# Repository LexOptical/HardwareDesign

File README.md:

# HardwareDesign
The LEX hardware design, electrical and mechanical

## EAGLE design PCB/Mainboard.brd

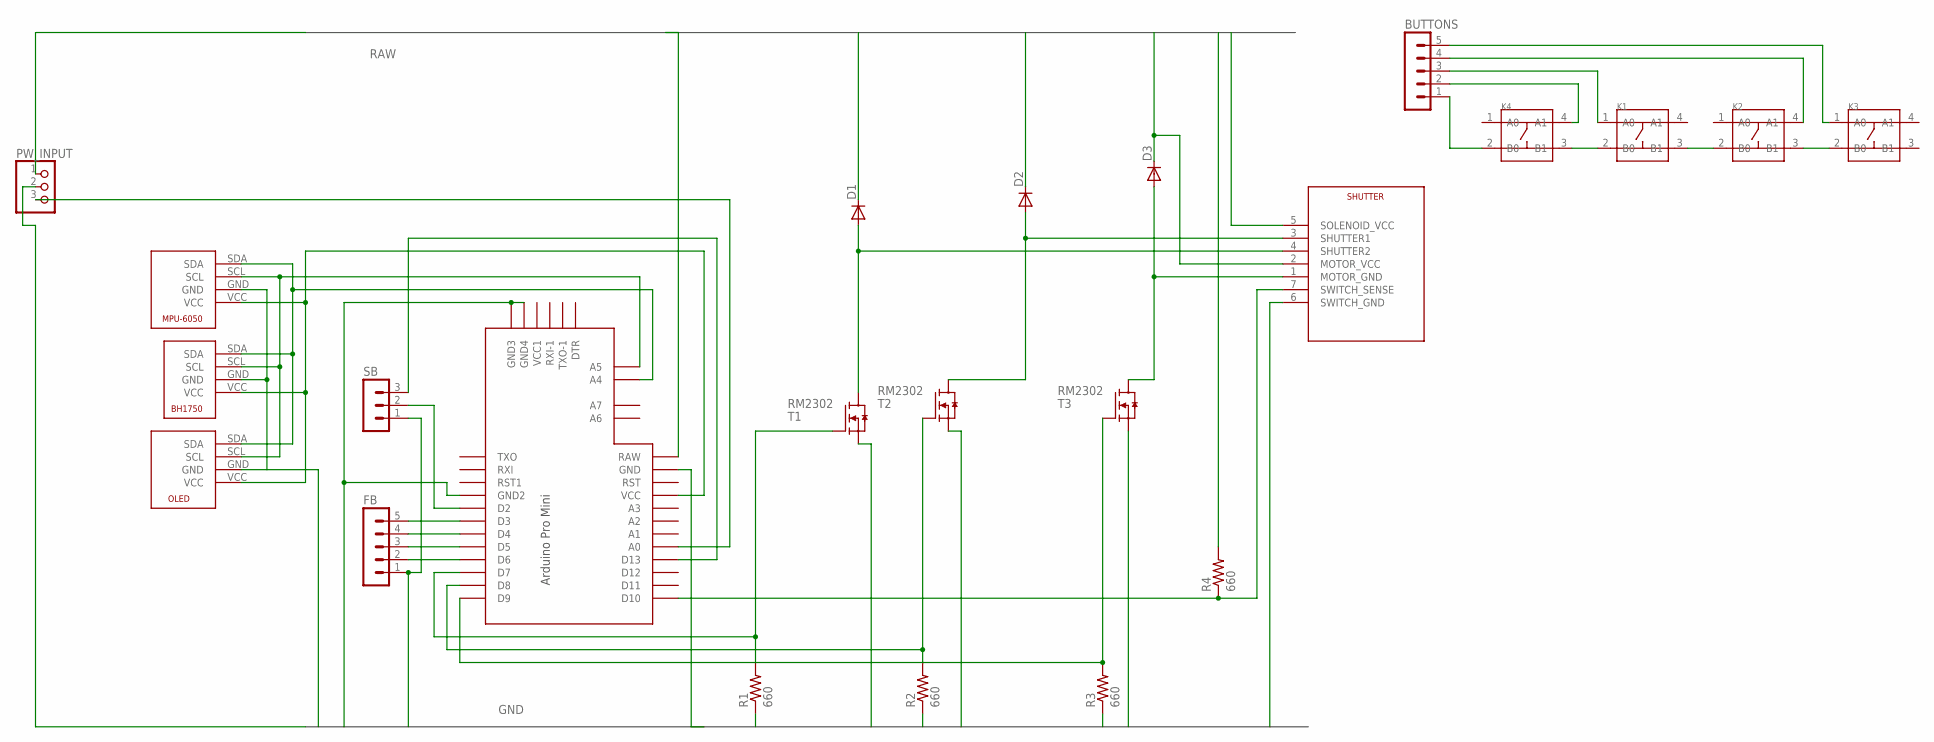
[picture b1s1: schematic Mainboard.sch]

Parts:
BH1750: BH1750; MA04-1
BUTTONS: MA05-1
D1, D2, D3: DIODE-D-5; D-5
FB: MA05-1
K1, K2, K3, K4: SMD-SWITCH-TACTILE-SPST-NO(4P-D6.0MM); SW4-SMD-6.0X6.0X5.0MM
MPU6050: MPU-6050; MA04-1
OLED: OLED; MA04-1
PW_INPUT: PINHD-1X3; 1X03
R1, R2, R3, R4: 660; 0204V
SB: MA03-1
T1, T2, T3: RM2302; SOT23
U$1: SHUTTER; MA07-1
U$7: PRO-MINI-2

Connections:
BAT_SENSE: PW_INPUT.3, U$7.A0
BTG: BUTTONS.1, K1.2 (B0), K1.3 (B1), K2.2 (B0), K2.3 (B1), K3.2 (B0), K4.2 (B0), K4.3 (B1)
GND: BH1750.GND, FB.1, MPU6050.GND, OLED.GND, PW_INPUT.2, R1.1, R2.1, R3.1, SB.1, T1.SOURCE (S), T2.SOURCE (S), T3.SOURCE (S), U$1.6 (SWITCH_GND), U$7.GND, U$7.GND1 (GND2), U$7.GND2 (GND3), U$7.GND3 (GND4)
M_GND: D3.A, T3.DRAIN (D), U$1.1 (MOTOR_GND)
unnamed: R3.2, T3.GATE (G), U$7.D9
unnamed: R2.2, T2.GATE (G), U$7.D8
unnamed: R1.2, T1.GATE (G), U$7.D7
unnamed: BUTTONS.2, K4.4 (A1)
unnamed: BUTTONS.3, K1.1 (A0)
unnamed: BUTTONS.4, K2.4 (A1)
unnamed: FB.2, U$7.D6
unnamed: FB.3, U$7.D5
unnamed: FB.4, U$7.D4
unnamed: FB.5, U$7.D3
unnamed: BUTTONS.5, K3.1 (A0)
unnamed: SB.2, U$7.D2
unnamed: SB.3, U$7.D13
unnamed: BH1750.VCC, MPU6050.VCC, OLED.VCC, U$7.VCC
S1: D2.A, T2.DRAIN (D), U$1.3 (SHUTTER1)
S2: D1.A, T1.DRAIN (D), U$1.4 (SHUTTER2)
SCL: BH1750.SCL, MPU6050.SCL, OLED.SCL, U$7.A5
SDA: BH1750.SDA, MPU6050.SDA, OLED.SDA, U$7.A4
SENSE: R4.1, U$1.7 (SWITCH_SENSE), U$7.D10
VCC: D1.C, D2.C, D3.C, PW_INPUT.1, R4.2, U$1.2 (MOTOR_VCC), U$1.5 (SOLENOID_VCC), U$7.RAW

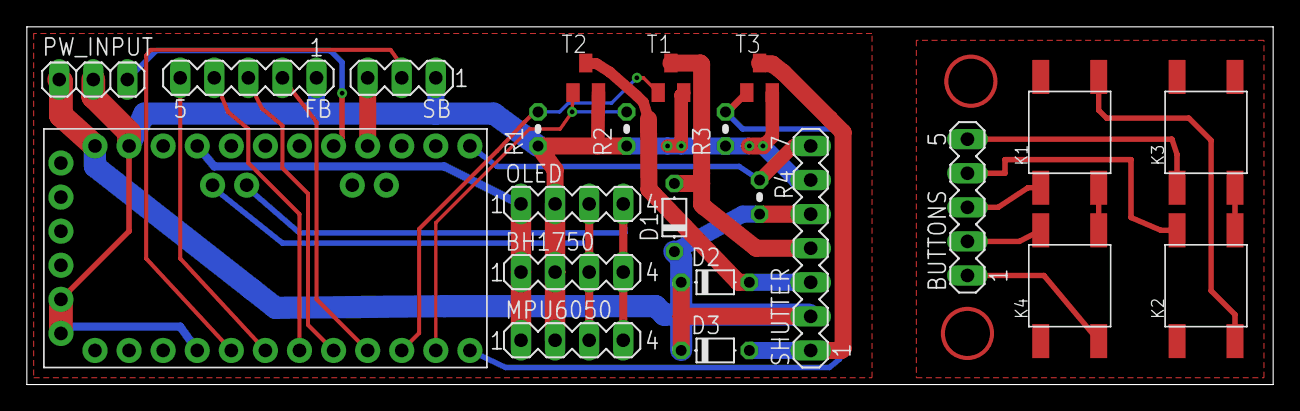
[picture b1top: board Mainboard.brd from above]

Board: 2 copper layers, 92.9 x 26.7 mm, 23 parts (0 on the bottom side), 24 nets.

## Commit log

2018-07-06 LEX parametric viewfinder
2018-07-06 STL files and Github content
2018-07-14 The whole camera ready to import to your fusion workspace
2018-07-19 PCB design added. NOTE transistors are miswired
2018-07-20 Add vias to get around the transistor routing issue
2018-07-20 Add voltage sense line for battery
2018-07-20 Clear a couple of clearance errors
2020-10-18 Include STEP file, update Fusion360 file to include back stiffening insert
